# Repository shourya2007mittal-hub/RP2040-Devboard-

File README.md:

# RP2040-Devboard-

SO I made a custom Rp2040 Dev-board for myself . I tried to make a dev board in which I have the access to almost all the gpio/analog pins available on the Rp2040 . It also holds an USB-C Type interference for communication and 3.3V Voltage regulator and Crystal oscillator , Flash Memory , boot pin and LEDS and battery connector and more.

## Features

- Based on RP-2040 Chip
- Has MCP1700x-330xxTT as Voltage Regualtor 
- Has W25Q16JVUXIQTR as Flash Memory
- Uses 2 set of 18 connector pins
- Has on-Board LEDS and battery connector 

## Cost Summary (BOM)

| Item | Quantity | Price (USD) | Source |
|------|------------|------------|---------|
| PCB + PCBA + Shipping  | 1 | $83.94 | JLCPCB |

**Total Estimated Cost:** **$83.94**

### Schematic

### PCB Design

### 3D Design

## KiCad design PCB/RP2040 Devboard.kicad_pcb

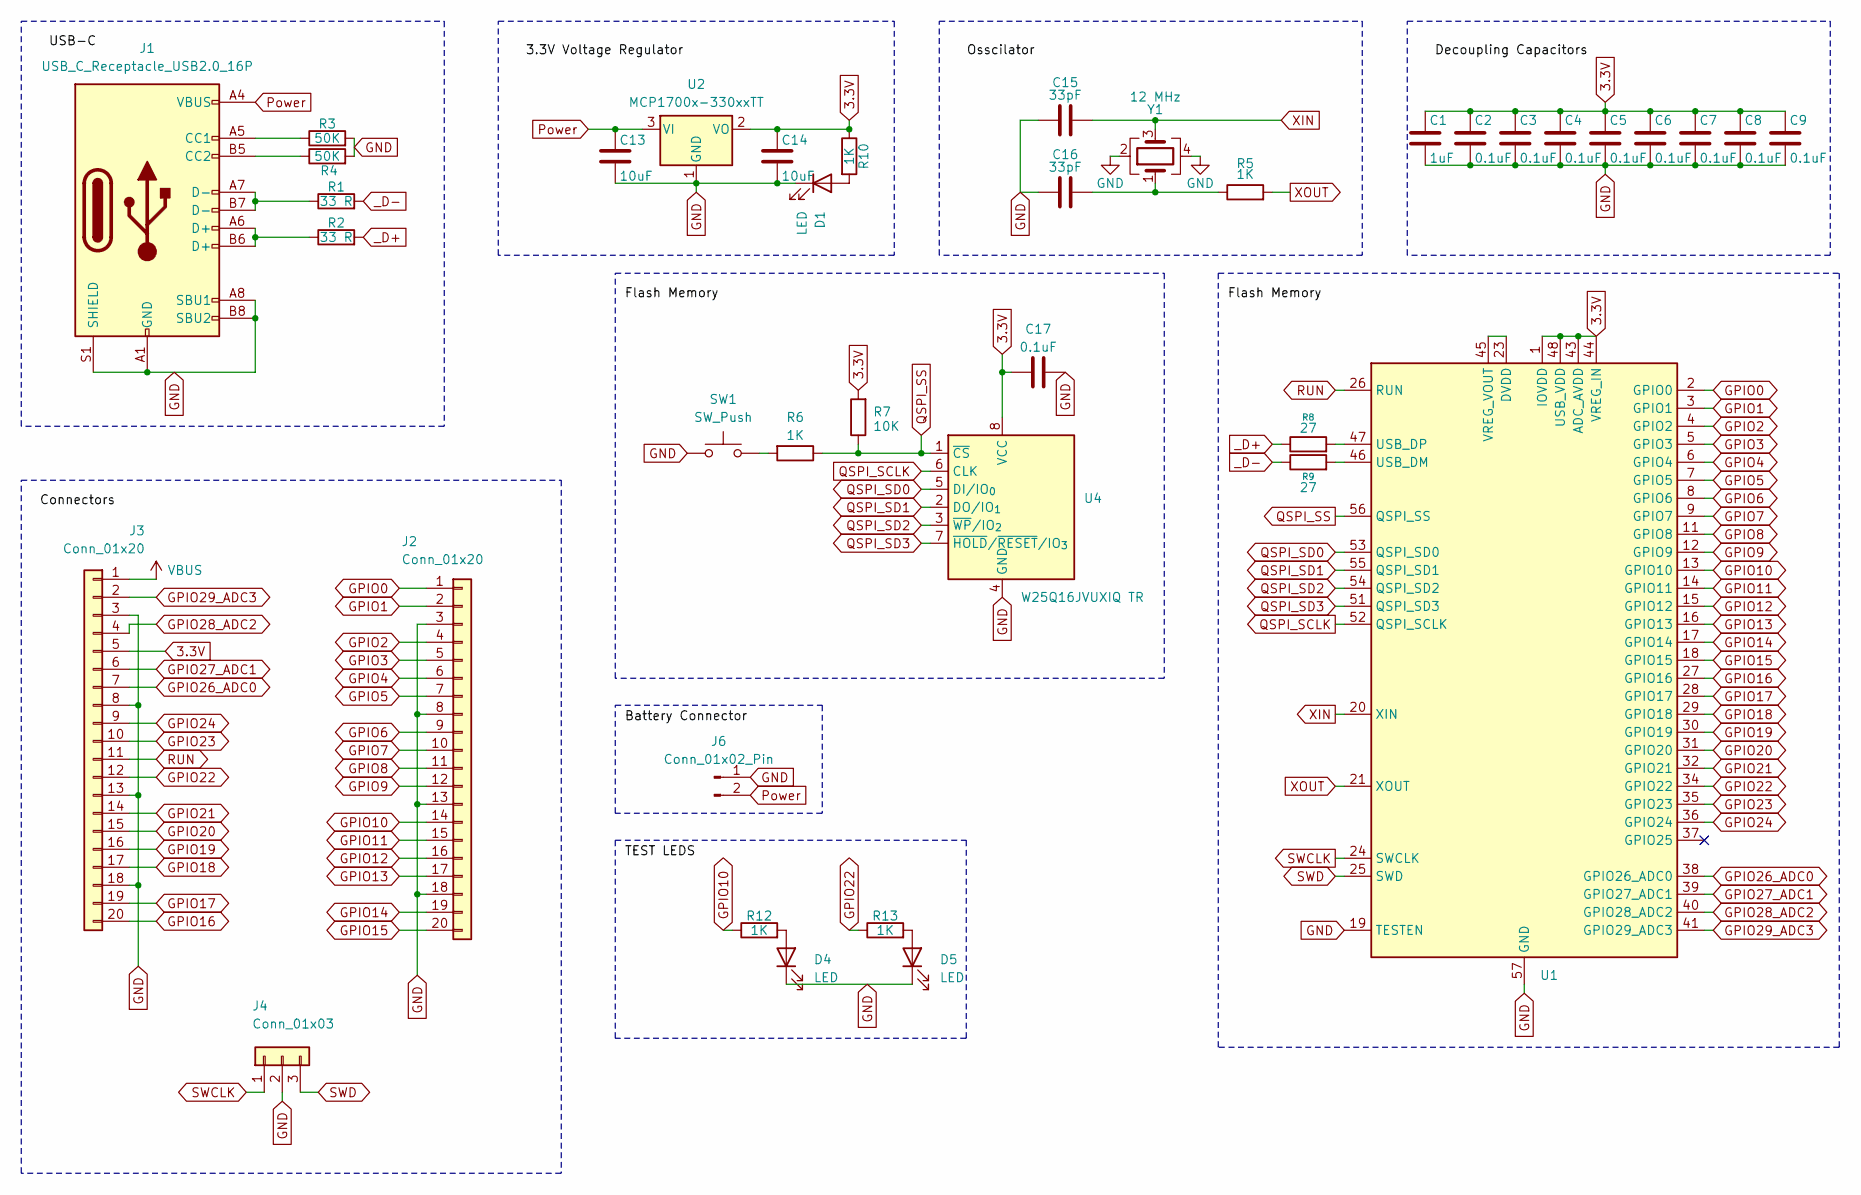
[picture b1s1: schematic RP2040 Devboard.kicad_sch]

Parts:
C1: 1uF; C_0402_1005Metric
C2, C3, C4, C5, C6, C7, C8, C9, C17: 0.1uF; C_0402_1005Metric
C13, C14: 10uF; C_0603_1608Metric
C15, C16: 33pF; C_0402_1005Metric
D1, D4, D5: LED; LED_0201_0603Metric
J1: USB_C_Receptacle_USB2.0_16P; USB_C_Receptacle_G-Switch_GT-USB-7010ASV
J2, J3: Conn_01x20; PinHeader_1x20_P2.54mm_Vertical
J4: Conn_01x03; PinHeader_1x03_P2.54mm_Vertical
J6: Conn_01x02_Pin; Hirose_DF13-02P-1.25DSA_1x02_P1.25mm_Vertical
R1, R2: 33 R; C_0603_1608Metric
R3, R4: 50K; C_0603_1608Metric
R5, R6: 1K; R_0402_1005Metric
R7: 10K; R_0402_1005Metric
R8, R9: 27; R_0402_1005Metric
R10, R12, R13: 1K; R_0603_1608Metric
SW1: SW_Push; SW_Push_SPST_NO_Alps_SKRK
U1: RP2040; QFN-56-1EP_7x7mm_P0.4mm_EP3.2x3.2mm
U2: MCP1700x-330xxTT; SOT-23
U4: W25Q16JVUXIQ TR; Winbond_USON-8-1EP_3x2mm_P0.5mm_EP0.2x1.6mm
Y1: 12 MHz; Crystal_SMD_3225-4Pin_3.2x2.5mm

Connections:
3.3V: C1.1, C2.1, C3.1, C4.1, C5.1, C6.1, C7.1, C8.1, C9.1, C14.1, C17.1, J3.5, R7.2, R10.1, U1.1 (IOVDD), U1.10 (IOVDD), U1.22 (IOVDD), U1.33 (IOVDD), U1.42 (IOVDD), U1.43 (ADC_AVDD), U1.44 (VREG_IN), U1.48 (USB_VDD), U1.49 (IOVDD), U2.2 (VO), U4.8 (VCC)
GND: C1.2, C2.2, C3.2, C4.2, C5.2, C6.2, C7.2, C8.2, C9.2, C13.2, C14.2, C15.1, C16.1, C17.2, D1.1 (K), D4.1 (K), D5.1 (K), J1.A1 (GND), J1.A8 (SBU1), J1.A12 (GND), J1.B1 (GND), J1.B8 (SBU2), J1.B12 (GND), J1.S1 (SHIELD), J2.3, J2.8, J2.13, J2.18, J3.3, J3.8, J3.13, J3.18, J4.2, J6.1, R3.2, R4.2, SW1.1, U1.19 (TESTEN), U1.57 (GND), U2.1 (GND), U4.4 (GND), Y1.2, Y1.4
GPIO0: J2.1, U1.2 (GPIO0)
GPIO1: J2.2, U1.3 (GPIO1)
GPIO2: J2.4, U1.4 (GPIO2)
GPIO3: J2.5, U1.5 (GPIO3)
GPIO4: J2.6, U1.6 (GPIO4)
GPIO5: J2.7, U1.7 (GPIO5)
GPIO6: J2.9, U1.8 (GPIO6)
GPIO7: J2.10, U1.9 (GPIO7)
GPIO8: J2.11, U1.11 (GPIO8)
GPIO9: J2.12, U1.12 (GPIO9)
GPIO10: J2.14, R12.1, U1.13 (GPIO10)
GPIO11: J2.15, U1.14 (GPIO11)
GPIO12: J2.16, U1.15 (GPIO12)
GPIO13: J2.17, U1.16 (GPIO13)
GPIO14: J2.19, U1.17 (GPIO14)
GPIO15: J2.20, U1.18 (GPIO15)
GPIO16: J3.20, U1.27 (GPIO16)
GPIO17: J3.19, U1.28 (GPIO17)
GPIO18: J3.17, U1.29 (GPIO18)
GPIO19: J3.16, U1.30 (GPIO19)
GPIO20: J3.15, U1.31 (GPIO20)
GPIO21: J3.14, U1.32 (GPIO21)
GPIO22: J3.12, R13.1, U1.34 (GPIO22)
GPIO23: J3.10, U1.35 (GPIO23)
GPIO24: J3.9, U1.36 (GPIO24)
GPIO26_ADC0: J3.7, U1.38 (GPIO26_ADC0)
GPIO27_ADC1: J3.6, U1.39 (GPIO27_ADC1)
GPIO28_ADC2: J3.4, U1.40 (GPIO28_ADC2)
GPIO29_ADC3: J3.2, U1.41 (GPIO29_ADC3)
unnamed: C16.2, R5.1, Y1.1
unnamed: D1.2 (A), R10.2
unnamed: D4.2 (A), R12.2
unnamed: D5.2 (A), R13.2
unnamed: J1.A5 (CC1), R3.1
unnamed: J1.B5 (CC2), R4.1
unnamed: J1.A6 (D+), J1.B6 (D+), R2.1
unnamed: J1.A7 (D-), J1.B7 (D-), R1.1
unnamed: R6.2, SW1.2
unnamed: R9.2, U1.46 (USB_DM)
unnamed: R8.2, U1.47 (USB_DP)
unnamed: U1.23 (DVDD), U1.45 (VREG_VOUT), U1.50 (DVDD)
Power: C13.1, J1.A4 (VBUS), J1.A9 (VBUS), J1.B4 (VBUS), J1.B9 (VBUS), J6.2, U2.3 (VI)
QSPI_SCLK: U1.52 (QSPI_SCLK), U4.6 (CLK)
QSPI_SD0: U1.53 (QSPI_SD0), U4.5 (DI/IO_{0})
QSPI_SD1: U1.55 (QSPI_SD1), U4.2 (DO/IO_{1})
QSPI_SD2: U1.54 (QSPI_SD2), U4.3 (~WP/IO_{2})
QSPI_SD3: U1.51 (QSPI_SD3), U4.7 (~HOLD/~RESET/IO_{3})
QSPI_SS: R6.1, R7.1, U1.56 (QSPI_SS), U4.1 (~CS)
RUN: J3.11, U1.26 (RUN)
SWCLK: J4.1, U1.24 (SWCLK)
SWD: J4.3, U1.25 (SWD)
VBUS: J3.1
XIN: C15.2, U1.20 (XIN), Y1.3
XOUT: R5.2, U1.21 (XOUT)
_D+: R2.2, R8.1
_D-: R1.2, R9.1

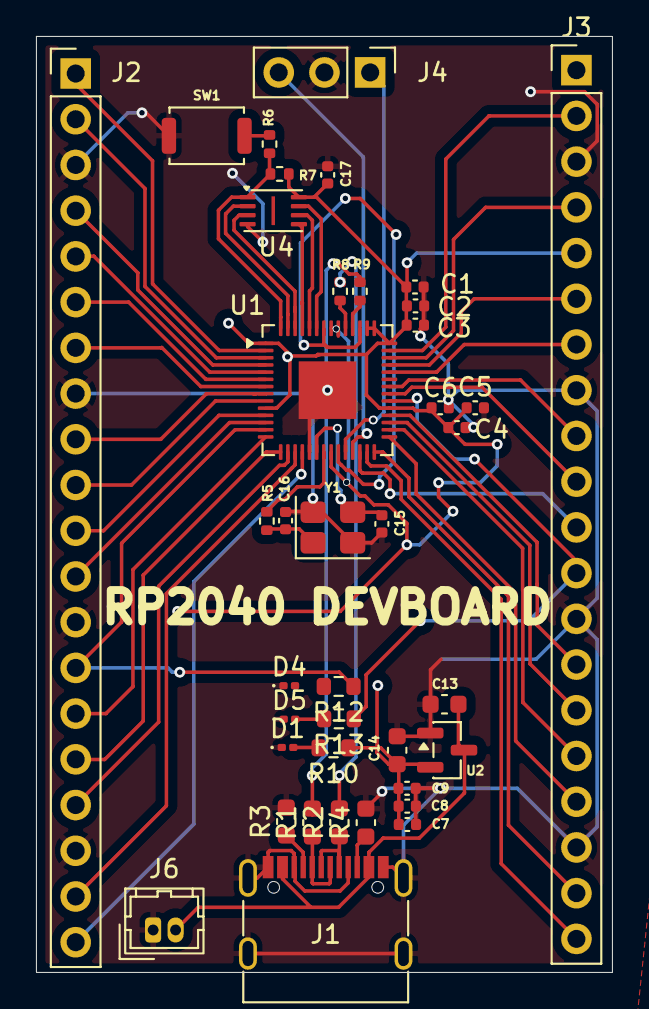
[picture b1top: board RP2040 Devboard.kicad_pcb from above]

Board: 2 copper layers, 32.0 x 52.0 mm, 39 parts (0 on the bottom side), 57 nets.

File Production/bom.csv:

Designator,Footprint,Quantity,Value,LCSC Part #
C1,0402,1,1uF,
"C13, C14",0603,2,10uF,
"C15, C16",0402,2,33pF,
"C17, C2, C3, C4, C5, C6, C7, C8, C9",0402,9,0.1uF,
"D1, D4, D5",0201,3,LED,
J1,USB_C_Receptacle_G-Switch_GT-USB-7010ASV,1,USB_C_Receptacle_USB2.0_16P,
"J2, J3",PinHeader_1x20_P2.54mm_Vertical,2,Conn_01x20,
J4,PinHeader_1x03_P2.54mm_Vertical,1,Conn_01x03,
J6,Hirose_DF13-02P-1.25DSA_1x02_P1.25mm_Vertical,1,Conn_01x02_Pin,
"R1, R2",0603,2,33 R,
"R10, R12, R13",0603,3,1K,
"R3, R4",0603,2,50K,
"R5, R6",0402,2,1K,
R7,0402,1,10K,
"R8, R9",0402,2,27,
SW1,SW_Push_SPST_NO_Alps_SKRK,1,SW_Push,
U1,QFN-56-1EP_7x7mm_P0.4mm_EP3.2x3.2mm,1,RP2040,
U2,SOT-23,1,MCP1700x-330xxTT,
U4,Winbond_USON-8-1EP_3x2mm_P0.5mm_EP0.2x1.6mm,1,W25Q16JVUXIQ TR,
Y1,Crystal_SMD_3225-4Pin_3.2x2.5mm,1,12 MHz,
